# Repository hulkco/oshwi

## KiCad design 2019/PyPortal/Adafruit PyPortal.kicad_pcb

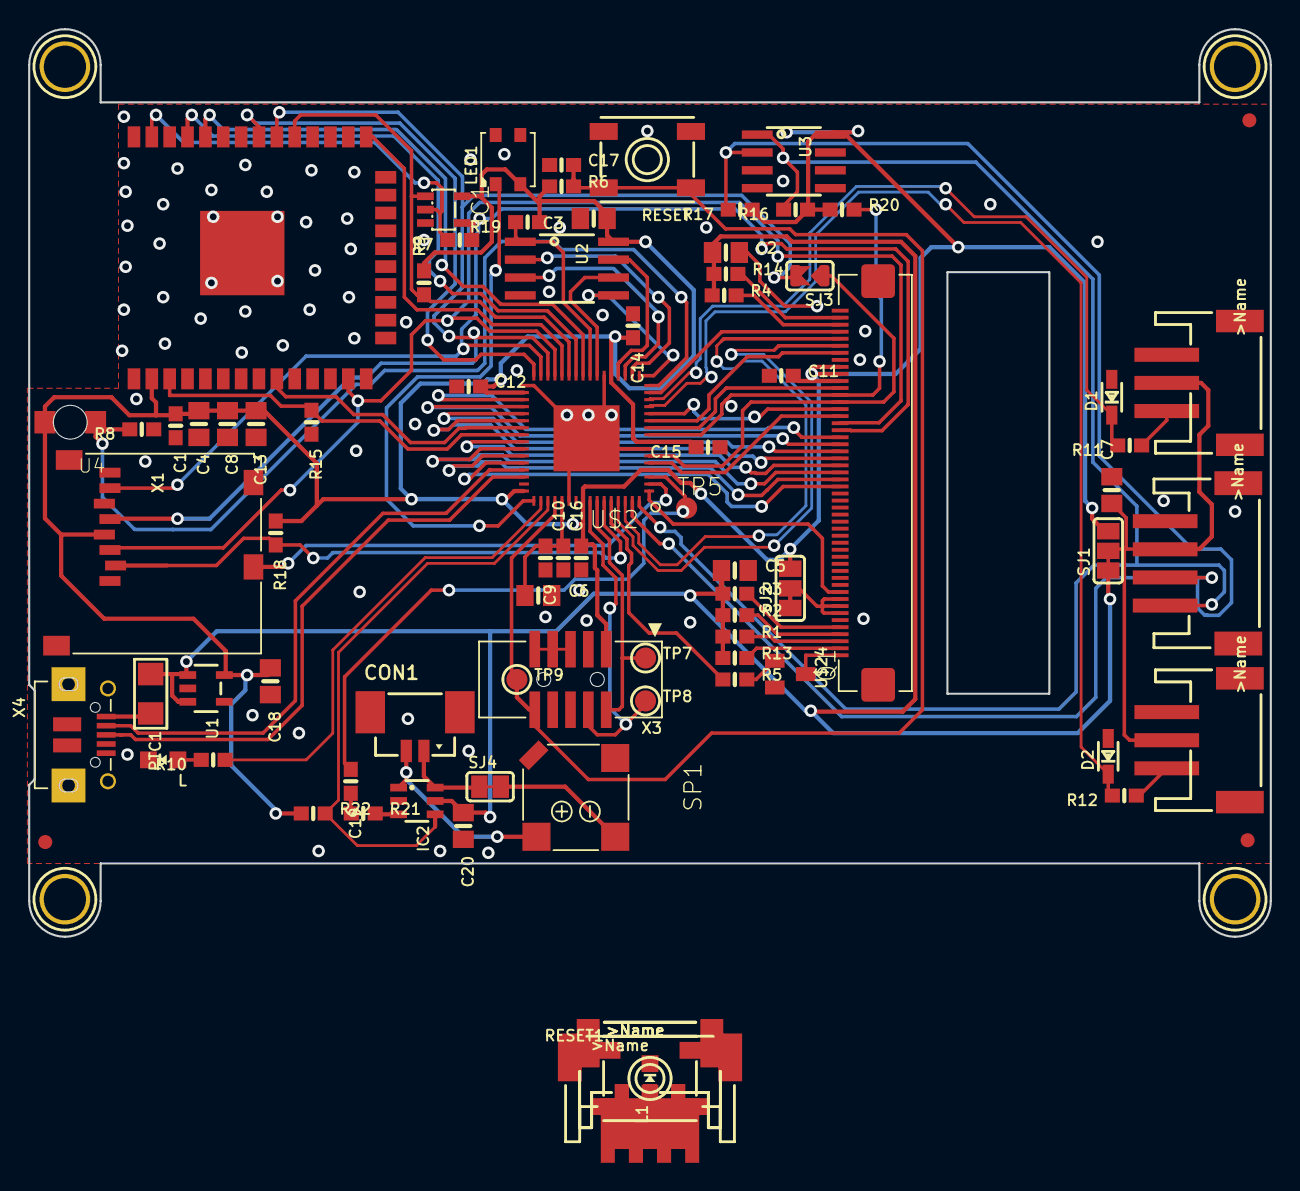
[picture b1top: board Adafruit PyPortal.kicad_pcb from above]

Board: 16 copper layers, 88.3 x 64.5 mm, 86 parts (0 on the bottom side), 8 nets.

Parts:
C1, C17, C19: 0.1uF; 0603-NO
C2, C3, C5, C6, C7, C8, C13, C18, C20: 10uF; 0805-NO
C4: 0.1uF; 0805-NO
C9: 1uF; 0603-NO
C10, C11, C12, C14, C15, C16: .1u; 0603-NO
CON1: CON_MOLEX_2P; 53398-0271
D1, D2: 3.6V; SOD-323
I2C, I2C1: JST PH 4; JSTPH4
IC1: 74AHC1G125; SOT23-5L
IC2: PAM8301; SOT23-6
L, L1: RED; CHIPLED_0805_NOOUTLINE
LED1: WS2812B3535; LED3535
NEOPIX, NEOPIX1: JST PH 3; JSTPH3
PTC1: 500mA; 1206
Q1: MMBT2222; SOT23-BEC
R1, R2, R3, R4, R13, R14: 100; 0603-NO
R5, R10, R11, R12: 1K; 0603-NO
R6, R8, R9, R15, R16, R17, R18, R19, R20: 10K; 0603-NO
R7: DNP; 0603-NO
R21, R22: 47K; 0603-NO
RESET, RESET1: EVQQ 6mm; EVQ-Q2_SMALLER
SENSE, SENSE1: JST PH 3; JSTPH3
SJ1, SJ2: SOLDERJUMPER_2WAY; SOLDERJUMPER_2WAY_OPEN_NOPASTE
SJ3: SOLDERJUMPER; SOLDERJUMPER_ARROW_NOPASTE
SJ4: SOLDERJUMPERCLOSED; SOLDERJUMPER_CLOSEDWIRE
SP1: 7.5mm SPK; BUZZER_SMT_7.5MM
TP5: TPTP15R; TP15R
TP7, TP8, TP9: TESTPOINTROUND1.5MM; TESTPOINT_ROUND_1.5MM
U1: AP2112-3.3; SOT23-5
U2: GD25Q64; SOIC8_208MIL
U3: ADT7410; SOIC8_150MIL
U4: ALS-PT21; ALS-PT26-21C
U$2: ATSAMD51J20; PQFN64-1
U$7, U$15, U$16, U$17: MOUNTINGHOLE3.0THIN; MOUNTINGHOLE_3.0_PLATEDTHIN
U$9, U$11, U$23: FIDUCIAL_1MM
U$24: DISP_LCD_6LED_240X320_50PIN; TFT_3.2IN_240X320_50PIN
X1: microSD; MICROSD
X3: 2x5 0.05" SWD; 2X05_1.27MM_BOX_POSTS
X4: microUSB; 4UCONN_20329_V2
X6: ESP32_WROOM32; WROOM32

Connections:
/Adafruit PyPortal_1/~RESET: RESET.B, RESET.B', RESET1.B, RESET1.B'
GND: I2C.1, I2C.NC1, I2C.NC2, I2C1.1, I2C1.NC1, I2C1.NC2, L.C, L1.C, NEOPIX.1, NEOPIX1.1, RESET.A, RESET.A', RESET1.A, RESET1.A', SENSE.1, SENSE1.1
unnamed: L.A, L1.A
unnamed: NEOPIX.3, NEOPIX1.3
unnamed: SENSE.3, SENSE1.3
SCL: I2C.4, I2C1.4
SDA: I2C.3, I2C1.3
VCC: I2C.2, I2C1.2, NEOPIX.2, NEOPIX1.2, SENSE.2, SENSE1.2

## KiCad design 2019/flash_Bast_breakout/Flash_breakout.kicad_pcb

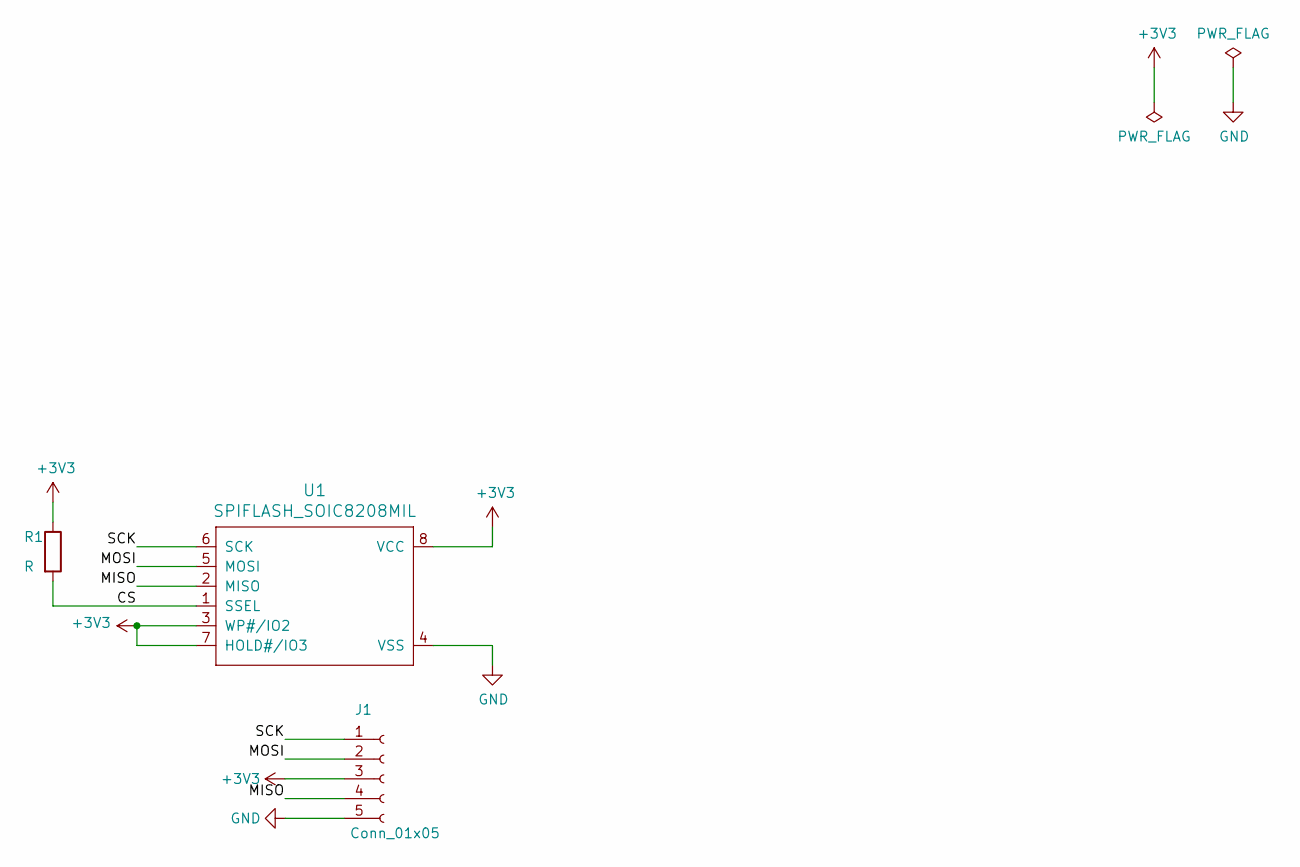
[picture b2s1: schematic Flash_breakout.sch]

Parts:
J1: Conn_01x05; PinSocket_1x05_P2.54mm_Vertical
R1: R; R_0805_2012Metric_Pad1.15x1.40mm_HandSolder
U1: SPIFLASH_SOIC8208MIL; SOIC-8_3.9x4.9mm_P1.27mm

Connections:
+3V3: J1.3, R1.1, U1.3 (WP#/IO2), U1.7 (HOLD#/IO3), U1.8 (VCC)
/CS: R1.2, U1.1 (SSEL)
/MISO: J1.4, U1.2 (MISO)
/MOSI: J1.2, U1.5 (MOSI)
/SCK: J1.1, U1.6 (SCK)
GND: J1.5, U1.4 (VSS)

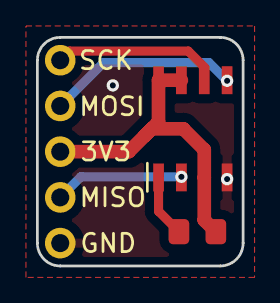
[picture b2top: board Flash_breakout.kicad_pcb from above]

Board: 2 copper layers, 11.4 x 12.7 mm, 3 parts (0 on the bottom side), 6 nets.

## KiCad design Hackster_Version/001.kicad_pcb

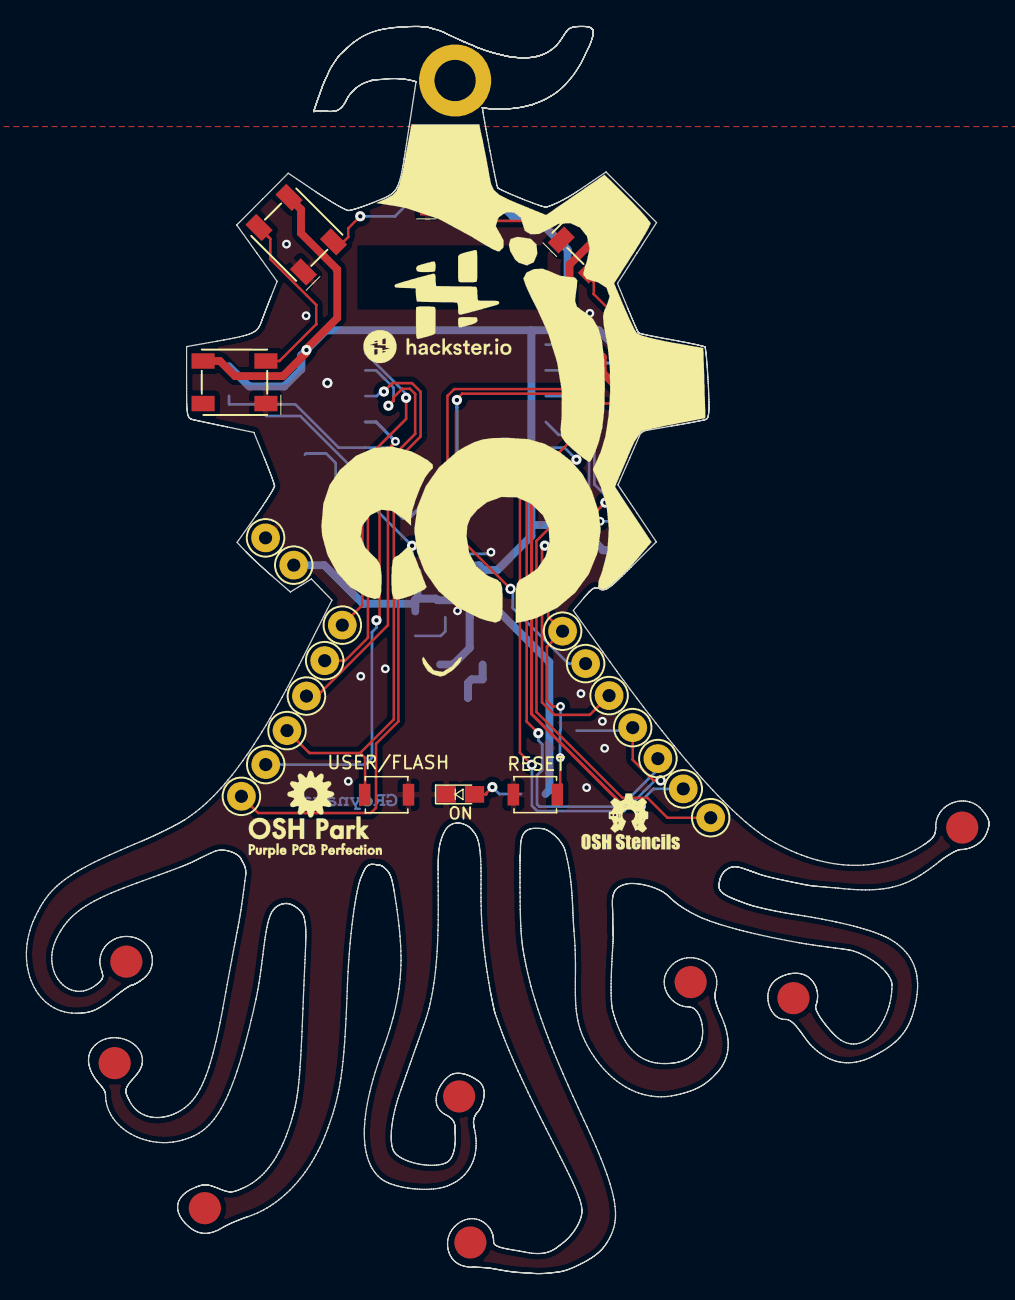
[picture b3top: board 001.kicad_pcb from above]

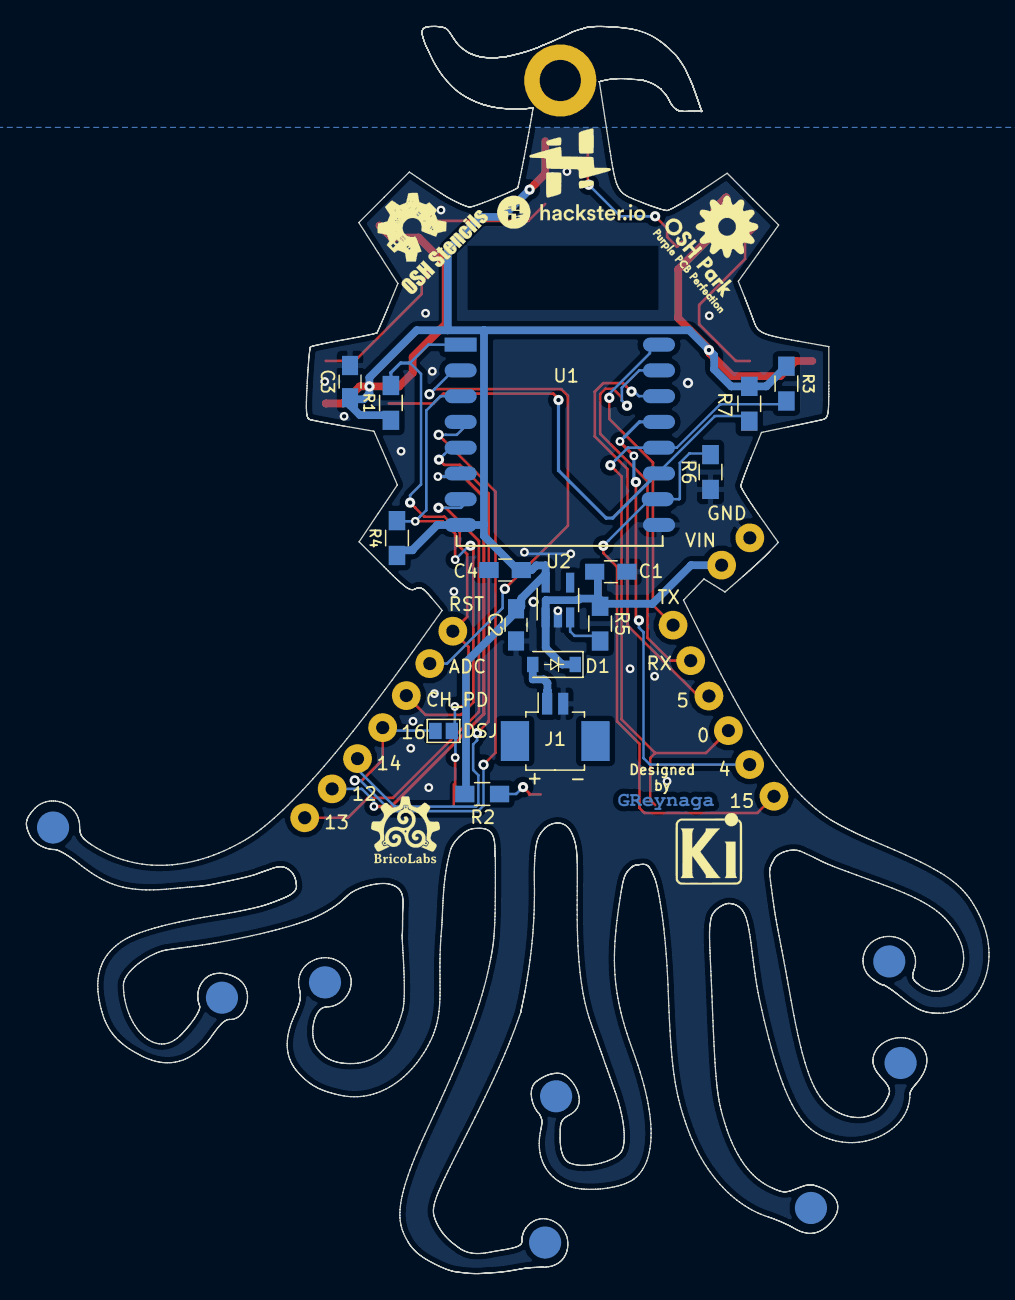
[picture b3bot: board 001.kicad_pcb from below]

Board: 2 copper layers, 74.7 x 96.8 mm, 67 parts (21 on the bottom side), 24 nets.

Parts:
B-G***: B-LOGO; bricolabs-14
C1, C2: 10uF; C_0805_HandSoldering
C3: 22nF; C_0805_HandSoldering
C4: 1uF; C_0805_HandSoldering
D1: MBRA140; D_SOD-123
D2: ON; LED_0805
Eyes***: LOGO; Oshwdem_Eyes_08
GBSilk***: LOGO; greynaga6-2
GS***: v; greynaga6-2-cooper
H2G***: H2-LOGO; hackster-h-900
H-G***: H-LOGO; hackster-h-700
Head***: LOGO; Oshwdem_Head_01
IO-G***: IO-LOGO; hackster-io-2100
IO-G***#2: IO-LOGO; hackster-io-2100
J1: CONN_01X02; Molex_PicoBlade_53261-0271_02x1.25mm_Angled
J2, J3, J4, J5, J6, J7, J8, J9, J10, J11, J12, J13, J14, J15, J16: TEST_1P; CONN-HEADER-STRAIGHT-P2.54MM-1x01
J17: GS2
LED1, LED2, LED3, LED4, LED5: WS2812B
Mouth***: LOGO; Oshwdem_Mouth_01
Os1***: Os1-LOGO; OshStencil-3000
R1, R3, R4, R5, R6, R7: 10k; R_0805_HandSoldering
R2: 1k; R_0805_HandSoldering
REF1**, REF2**, REF3**, REF4**, REF5**, REF6**, REF7**, REF8**, REF9**, REF10**, REF11**, REF12**, REF13**, REF14**, REF15**, REF16**: PADS
SW1: USER/PROG; SW_SPST_B3U-1000P
SW2: RESET; SW_SPST_B3U-1000P
Star1***: Star1-LOGO; OshStencil-Star-2000
U1: ESP-12; ESP-12S_SMD
U2: SPX3819M5-L-3-3/TR; SOT-23-5_HandSoldering

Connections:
+3.3V: C2.1, C3.1, C4.1, LED1.3, LED2.3, LED3.3, LED4.3, LED5.3, R1.1, R2.1, R3.1, R4.1, R7.1, U1.8, U2.5
ADC: J4.1, U1.2
CH_PD: J6.1, R4.2, U1.3
GND: C1.2, C2.2, C3.2, C4.2, D2.1, J1.2, J16.1, LED1.1, LED2.1, LED3.1, LED4.1, LED5.1, R6.1, SW1.1, SW2.1, U1.9, U2.2
GPIO0: J11.1, R3.2, SW1.2, U1.12
GPIO2: LED1.2, R7.2, U1.11
GPIO4: J9.1, U1.13
GPIO5: J7.1, U1.14
GPIO12: J10.1, U1.6
GPIO13: J12.1, U1.7
GPIO14: J8.1, U1.5
GPIO15: J13.1, R6.2, U1.10
GPIO16: J14.1, J17.2, U1.4
unnamed: D2.2, R2.2
unnamed: LED1.4, LED2.2
unnamed: LED2.4, LED3.2
unnamed: LED3.4, LED4.2
unnamed: LED4.4, LED5.2
unnamed: R5.2, U2.3
REST: J2.1, J17.1, R1.2, SW2.2, U1.1
RXD: J5.1, U1.15
TXD: J3.1, U1.16
VBAT: D1.2, J1.1
VCC: C1.1, D1.1, J15.1, R5.1, U2.1

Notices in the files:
2019/flash_Bast_breakout/Flash_breakout.kicad_pcb:
Released under the CERN Open Hardware License v1.2
